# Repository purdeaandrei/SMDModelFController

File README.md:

# SMD Model F controller based on TH Xwhatsit design. ('kishsaver' variant)

This variant is for IBM 4704 keyboards, aka 'kishsaver' class model F keyboards, like F107, F50, F62, F77
This variant is not 100% compatible with the https://www.modelfkeyboards.com/ recreations of the F62/F77, because the pin pitch is different,
although it is electrically compatible with those too, if one decides to wire it up with individual wires.

For other variants see:
* https://github.com/purdeaandrei/SMDModelFController/tree/extra_columns
* https://github.com/purdeaandrei/SMD4704KishsaverClassModelFController
* https://github.com/listofoptions/TH-XWhatsIt

## Images

## Origins and license

This project is based on the Through-hole xwhatsit by listofoptions, which is un turn
based on the capsense controllers by XWhatsIt
(Tom Wong-Cornall). original liscencure holds, as well as CERN OSH
(compatible license).

original implementation of Tom Wong-Cornall's controller documented here

http://downloads.cornall.co/ibm-capsense-usb-web/ibm-capsense-usb.html

Working theory of operation is under the previous link.

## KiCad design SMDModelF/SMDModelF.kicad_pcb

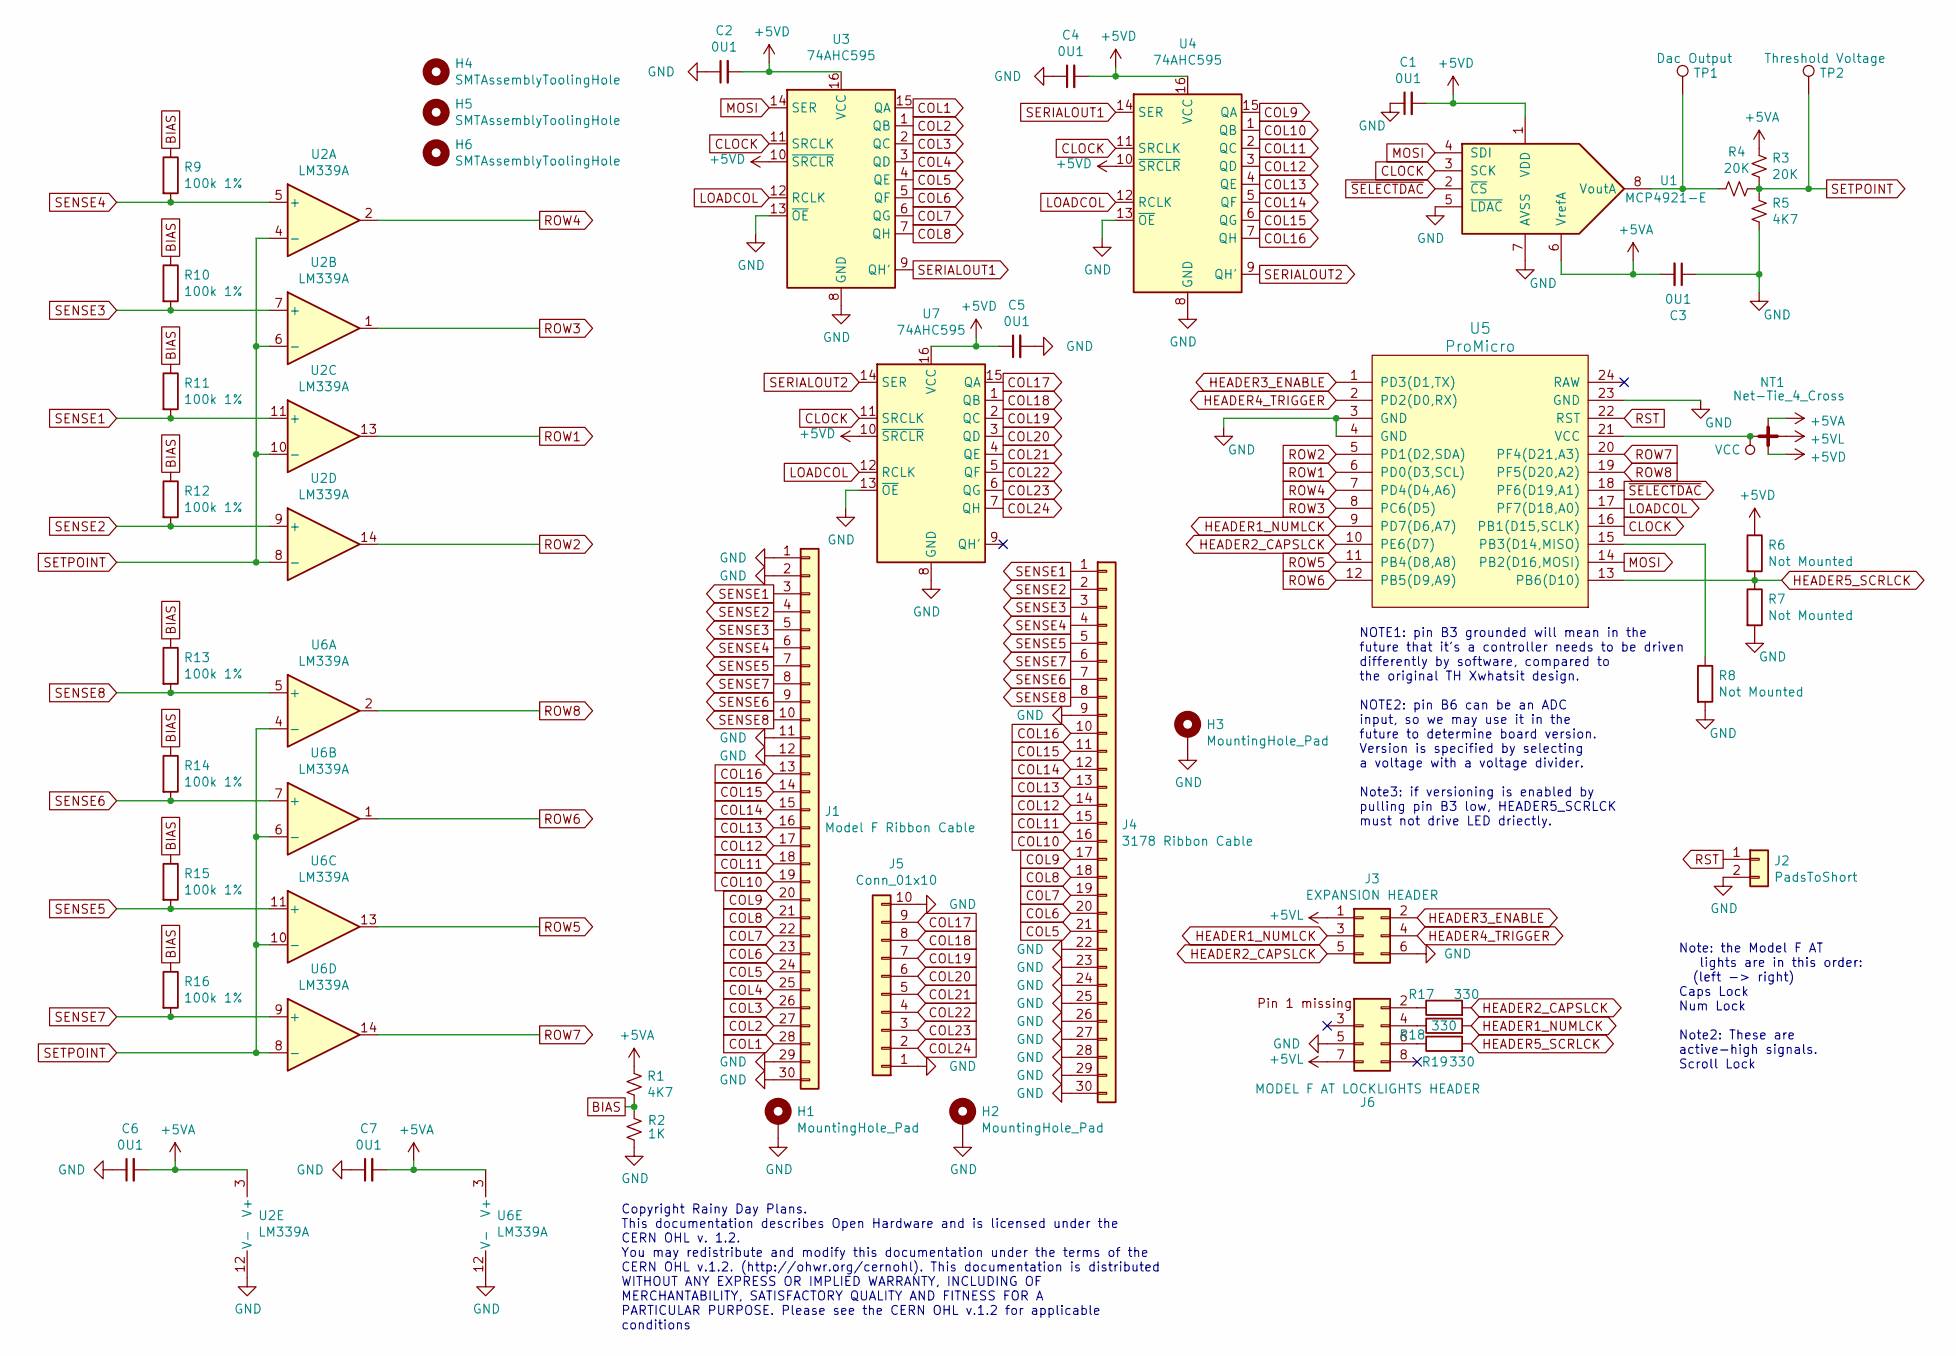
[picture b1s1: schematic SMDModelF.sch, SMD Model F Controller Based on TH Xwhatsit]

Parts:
C1, C2, C3, C4, C5, C6, C7: 0U1; C_0805_2012Metric_Pad1.15x1.40mm_HandSolder; LCSC C49678
H1: MountingHole_Pad; ModelF_new_mounting_hole_left
H2: MountingHole_Pad; ModelF_new_mounting_hole_right
H3: MountingHole_Pad; ChassisGnd
H4, H5, H6: SMTAssemblyToolingHole; tooling_hole
J1: Model F Ribbon Cable; Model_F_3.96mm_pitch_footprint
J2: PadsToShort
J3: EXPANSION HEADER; PinHeader_2x03_P2.54mm_Vertical_3dhorizontal
J4: 3178 Ribbon Cable; Model_F_3.96mm_pitch_footprint
J5: Conn_01x10; PinHeader_1x10_P2.54mm_Vertical
J6: MODEL F AT LOCKLIGHTS HEADER; FAT_LockLightsConnector
NT1: Net-Tie_4_Cross; NetTie-4_THT_Pad1.0mm
R1, R5: 4K7; R_0805_2012Metric_Pad1.15x1.40mm_HandSolder; LCSC C17673
R2: 1K; R_0805_2012Metric_Pad1.15x1.40mm_HandSolder; LCSC C17513
R3, R4: 20K; R_0805_2012Metric_Pad1.15x1.40mm_HandSolder; LCSC C4328
R6, R7, R8: Not Mounted; R_0805_2012Metric_Pad1.15x1.40mm_HandSolder
R9, R10, R11, R12, R13, R14, R15, R16: 100k 1%; R_0805_2012Metric_Pad1.15x1.40mm_HandSolder; LCSC C17407
R17, R18, R19: 330; R_0805_2012Metric_Pad1.15x1.40mm_HandSolder; LCSC C17630
TP1: Dac Output; TestPoint_Pad_D1.0mm
TP2: Threshold Voltage; TestPoint_Pad_D1.0mm
U1: MCP4921-E; SOIC-8_3.9x4.9mm_P1.27mm; LCSC C43499
U2, U6: LM339A; SOIC-14_3.9x8.7mm_P1.27mm; LCSC C74559
U3, U4, U7: 74AHC595; SOIC-16_3.9x9.9mm_P1.27mm; LCSC C5520
U5: ProMicro

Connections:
+5VA: C3.2, C6.2, C7.2, NT1.3, R1.1, R3.2, U1.6 (VrefA), U2.3 (V+), U6.3 (V+)
+5VD: C1.2, C2.2, C4.2, C5.1, NT1.4, R6.1, U1.1 (VDD), U3.10 (~SRCLR), U3.16 (VCC), U4.10 (~SRCLR), U4.16 (VCC), U7.10 (~SRCLR), U7.16 (VCC)
+5VL: J3.1, J6.7, NT1.2
BIAS: R1.2, R2.2, R9.1, R10.1, R11.1, R12.1, R13.1, R14.1, R15.1, R16.1
CLOCK: U1.3 (SCK), U3.11 (SRCLK), U4.11 (SRCLK), U5.16 (PB1(D15,SCLK)), U7.11 (SRCLK)
COL1: J1.28, U3.15 (QA)
COL2: J1.27, U3.1 (QB)
COL3: J1.26, U3.2 (QC)
COL4: J1.25, U3.3 (QD)
COL5: J1.24, J4.21, U3.4 (QE)
COL6: J1.23, J4.20, U3.5 (QF)
COL7: J1.22, J4.19, U3.6 (QG)
COL8: J1.21, J4.18, U3.7 (QH)
COL9: J1.20, J4.17, U4.15 (QA)
COL10: J1.19, J4.16, U4.1 (QB)
COL11: J1.18, J4.15, U4.2 (QC)
COL12: J1.17, J4.14, U4.3 (QD)
COL13: J1.16, J4.13, U4.4 (QE)
COL14: J1.15, J4.12, U4.5 (QF)
COL15: J1.14, J4.11, U4.6 (QG)
COL16: J1.13, J4.10, U4.7 (QH)
GND: C1.1, C2.1, C3.1, C4.1, C5.2, C6.1, C7.1, H1.1, H2.1, H3.1, J1.1, J1.2, J1.11, J1.12, J1.29, J1.30, J2.2, J3.6, J4.9, J4.22, J4.23, J4.24, J4.25, J4.26, J4.27, J4.28, J4.29, J4.30, J5.1, J5.10, J6.5, R2.1, R5.1, R7.2, R8.2, U1.5 (~LDAC~), U1.7 (AVSS), U2.12 (V-), U3.8 (GND), U3.13 (~OE), U4.8 (GND), U4.13 (~OE), U5.3 (GND), U5.4 (GND), U5.23 (GND), U6.12 (V-), U7.8 (GND), U7.13 (~OE)
HEADER1_NUMLCK: J3.3, R18.2, U5.9 (PD7(D6,A7))
HEADER2_CAPSLCK: J3.5, R17.2, U5.10 (PE6(D7))
HEADER3_ENABLE: J3.2, U5.1 (PD3(D1,TX))
HEADER4_TRIGGER: J3.4, U5.2 (PD2(D0,RX))
HEADER5_SCRLCK: R6.2, R7.1, R19.2, U5.13 (PB6(D10))
LOADCOL: U3.12 (RCLK), U4.12 (RCLK), U5.17 (PF7(D18,A0)), U7.12 (RCLK)
MOSI: U1.4 (SDI), U3.14 (SER), U5.14 (PB2(D16,MOSI))
unnamed: J5.2, U7.7 (QH)
unnamed: J5.3, U7.6 (QG)
unnamed: J5.4, U7.5 (QF)
unnamed: J5.5, U7.4 (QE)
unnamed: J5.6, U7.3 (QD)
unnamed: J5.7, U7.2 (QC)
unnamed: J5.8, U7.1 (QB)
unnamed: J5.9, U7.15 (QA)
unnamed: J6.2, R17.1
unnamed: J6.4, R18.1
unnamed: J6.6, R19.1
unnamed: R4.2, TP1.1, U1.8 (VoutA)
unnamed: R8.1, U5.15 (PB3(D14,MISO))
unnamed: U4.9 (QH'), U7.14 (SER)
ROW1: U2.13, U5.6 (PD0(D3,SCL))
ROW2: U2.14, U5.5 (PD1(D2,SDA))
ROW3: U2.1, U5.8 (PC6(D5))
ROW4: U2.2, U5.7 (PD4(D4,A6))
ROW5: U5.11 (PB4(D8,A8)), U6.13
ROW6: U5.12 (PB5(D9,A9)), U6.1
ROW7: U5.20 (PF4(D21,A3)), U6.14
ROW8: U5.19 (PF5(D20,A2)), U6.2
RST: J2.1, U5.22 (RST)
SENSE1: J1.3, J4.1, R11.2, U2.11 (+)
SENSE2: J1.4, J4.2, R12.2, U2.9 (+)
SENSE3: J1.5, J4.3, R10.2, U2.7 (+)
SENSE4: J1.6, J4.4, R9.2, U2.5 (+)
SENSE5: J1.7, J4.5, R15.2, U6.11 (+)
SENSE6: J1.9, J4.7, R14.2, U6.7 (+)
SENSE7: J1.8, J4.6, R16.2, U6.9 (+)
SENSE8: J1.10, J4.8, R13.2, U6.5 (+)
SERIALOUT1: U3.9 (QH'), U4.14 (SER)
SETPOINT: R3.1, R4.1, R5.2, TP2.1, U2.4 (-), U2.6 (-), U2.8 (-), U2.10 (-), U6.4 (-), U6.6 (-), U6.8 (-), U6.10 (-)
VCC: NT1.1, U5.21 (VCC)
~SELECTDAC: U1.2 (~CS~), U5.18 (PF6(D19,A1))

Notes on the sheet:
Copyright Rainy Day Plans. This documentation describes Open Hardware and is licensed under the CERN OHL v. 1.2. You may redistribute and modify this documentation under the terms of the CERN OHL v.1.2. (http://ohwr.org/cernohl). This documentation is distributed WITHOUT ANY EXPRESS OR IMPLIED WARR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
NOTE1: pin B3 grounded will mean in the future that it's a controller needs to be driven differently by software, compared to the original TH Xwhatsit design. NOTE2: pin B6 can be an ADC input, so we may use it in the future to determine board version. Version is specified by selecting a voltage wi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
Note: the Model F AT lights are in this order: (left -> right) Caps Lock Num Lock Note2: These are active-high signals. Scroll Lock

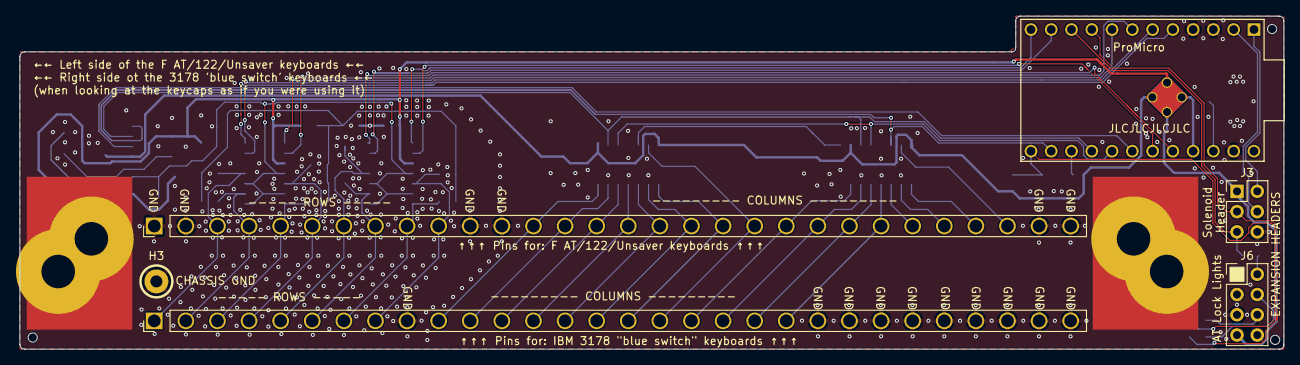
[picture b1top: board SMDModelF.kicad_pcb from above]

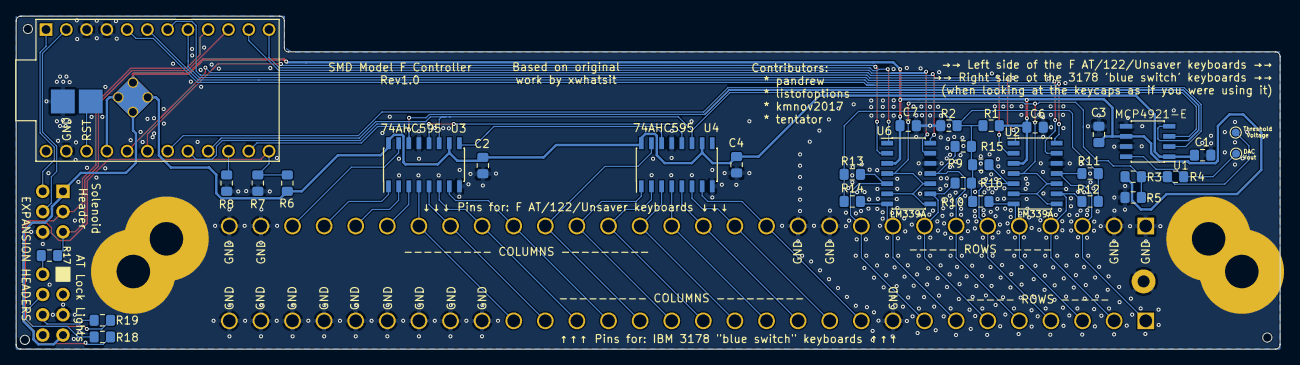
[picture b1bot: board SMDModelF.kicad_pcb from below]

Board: 2 copper layers, 158.4 x 41.7 mm, 45 parts (33 on the bottom side), 55 nets.

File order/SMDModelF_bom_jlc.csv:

"Comment","Designator","Footprint","LCSC Part #"
"0U1","C2,C3,C1,C4,C7,C6,C5","C_0805_2012Metric_Pad1.15x1.40mm_HandSolder","C49678"
"1K","R2","R_0805_2012Metric_Pad1.15x1.40mm_HandSolder","C17513"
"20K","R4,R3","R_0805_2012Metric_Pad1.15x1.40mm_HandSolder","C4328"
"4K7","R5,R1","R_0805_2012Metric_Pad1.15x1.40mm_HandSolder","C17673"
"100k 1%","R9,R10,R11,R12,R13,R14,R15,R16","R_0805_2012Metric_Pad1.15x1.40mm_HandSolder","C17407"
"330","R17,R19,R18","R_0805_2012Metric_Pad1.15x1.40mm_HandSolder","C17630"
"MCP4921-E","U1","SOIC-8_3.9x4.9mm_P1.27mm","C43499"
"LM339A","U2,U6","SOIC-14_3.9x8.7mm_P1.27mm","C74559"
"74AHC595","U3,U7,U4","SOIC-16_3.9x9.9mm_P1.27mm","C5520"

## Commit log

2020-09-30 First version of model F controller
2020-10-17 Added extra columns
2020-12-13 added 3d_default_libraries
2020-12-13 Added 3d model for locklights header, with missing pin.
2020-12-13 Added Pro Micro pins (symmetric metal length)
2020-12-13 Added vertical footprint, but with horizontal 3d part for solenoid driver header.
2020-12-13 Updated PCB file now everything points to correct 3d models.
2021-05-03 Updated pro micro schematic symbol, and added PDF schematics
2021-10-30 Removed proprietary datasheets
2021-10-30 Clarify license of card edge model
2021-10-30 Clarified license of the footprint library
2021-10-30 Clarified the license of some more files
2021-10-30 Updated Changes.txt
2021-10-30 Added another readme clarifying a license
2021-10-30 Ported over some changes from the 'standard' model F controller, to make 3d rendering look better
2021-10-30 Mark some components that are not supposed to be mounted virtual, for more correct 3d rendering.
2021-10-30 Added images, tweaked readme
2021-10-30 Added other variants links
2021-10-30 Mark some components virtual, add images of 3d renders, tweak readme
2021-10-30 Fix up Readme
2021-10-30 Revert "Fix up Readme"
    This reverts commit 2f16b72533ee77a87f0c5d946b99e5e82d292edd.
2022-02-14 Update component rotations, to match new behaviour of JLCPCB on the bottom layer
2022-07-31 Updated 100k resistor and shift register LCSC part numbers
2022-07-31 fix rotations to match latest JLCPCB behaviour
2022-09-15 Revert part of commit 'Updated 100k resistor and shift register LCSC part numbers' (the shift register BOM changes only)

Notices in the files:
SMDModelF/SMDModelF.kicad_pcb:
Licenced under CERN OHL Version 1.2
